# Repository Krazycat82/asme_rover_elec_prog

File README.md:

# ASME-rover-electrical
Circuits and code for ASME Rover team for 2023-24 year

Code for Motor Controllers

Sid was here

Mohamed was here.

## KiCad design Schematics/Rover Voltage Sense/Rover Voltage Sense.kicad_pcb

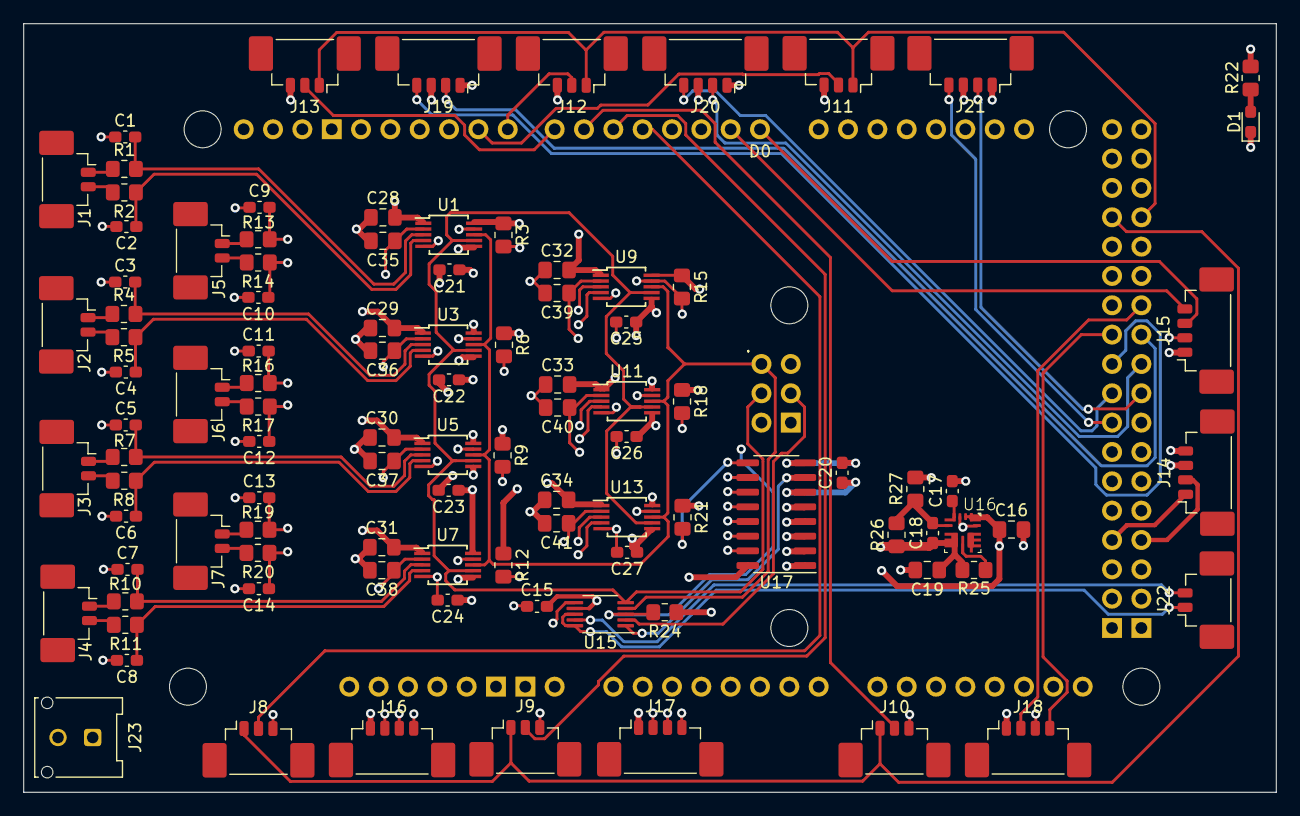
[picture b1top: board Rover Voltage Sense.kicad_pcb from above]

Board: 4 copper layers, 108.5 x 66.5 mm, 102 parts (0 on the bottom side), 77 nets.

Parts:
A1: Arduino_Mega2560_R3_Shield
C1, C2, C3, C4, C5, C6, C7, C8, C9, C10, C11, C12, C13, C14: 2.2n; C_0603_1608Metric_Pad1.08x0.95mm_HandSolder
C15: 100n; C_0603_1608Metric_Pad1.08x0.95mm_HandSolder
C16, C28, C29, C30, C31, C32, C33, C34: 10u; C_0805_2012Metric_Pad1.18x1.45mm_HandSolder
C17: 680p; C_0603_1608Metric_Pad1.08x0.95mm_HandSolder
C18: 10p; C_0603_1608Metric_Pad1.08x0.95mm_HandSolder
C19: 22u; C_0805_2012Metric_Pad1.18x1.45mm_HandSolder
C20, C21, C22, C23, C24, C25, C26, C27: 0.1u; C_0603_1608Metric_Pad1.08x0.95mm_HandSolder
C35, C36, C37, C38, C39, C40, C41: 1u; C_0805_2012Metric_Pad1.18x1.45mm_HandSolder
D1: LED; D_0603_1608Metric_Pad1.05x0.95mm_HandSolder
J1, J2, J3, J4, J5, J6, J7, J22: Conn_01x02; Molex_PicoBlade_53398-0271_1x02-1MP_P1.25mm_Vertical
J8, J9, J10, J11, J12, J13: Conn_01x03; Molex_PicoBlade_53398-0371_1x03-1MP_P1.25mm_Vertical
J14, J15, J16, J17, J18, J19, J20, J21: Conn_01x04; Molex_PicoBlade_53398-0471_1x04-1MP_P1.25mm_Vertical
J23: Conn_01x02; Molex_Micro-Fit_3.0_43045-0212_2x01_P3.00mm_Vertical
R1, R2, R4, R5, R7, R8, R10, R11, R13, R14, R16, R17, R19, R20: 15; R_0805_2012Metric_Pad1.20x1.40mm_HandSolder
R3, R6, R9, R12, R15, R18, R21: 10K; R_0805_2012Metric_Pad1.20x1.40mm_HandSolder
R22: 250; R_0805_2012Metric_Pad1.20x1.40mm_HandSolder
R24: 10k; R_0805_2012Metric_Pad1.20x1.40mm_HandSolder
R25, R27: 100k; R_0805_2012Metric_Pad1.20x1.40mm_HandSolder
R26: 200k; R_0805_2012Metric_Pad1.20x1.40mm_HandSolder
U1, U3, U5, U7, U9, U11, U13: MCP33151; MSOP-10_3x3mm_P0.5mm
U15: INA229; VSSOP-10_3x3mm_P0.5mm
U16: TPSM828512; QFN_FCMOD_RDY00009A
U17: 74HC138; SOIC-16_3.9x9.9mm_P1.27mm

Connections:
+1V8: C18.1, C19.1, C35.1, C36.1, C37.1, C38.1, C39.1, C40.1, C41.1, R25.1, R26.1, U1.2 (AVDD), U3.2 (AVDD), U5.2 (AVDD), U7.2 (AVDD), U9.2 (AVDD), U11.2 (AVDD), U13.2 (AVDD), U16.6 (VOUT)
+5V: A1.5V1 (5V), A1.5V3 (5V), A1.5V4 (5V), C15.2, C16.1, C20.1, C21.1, C22.1, C23.1, C24.1, C25.1, C26.1, C27.1, C28.2, C29.2, C30.2, C31.2, C32.2, C33.2, C34.2, J14.3, J15.1, J16.1, J17.1, J18.1, J19.1, J20.1, J21.1, J23.1, R3.1, R6.1, R9.1, R12.1, R15.1, R18.1, R21.1, R22.1, R24.1, U1.1 (Vref), U1.6 (SDI), U1.10 (DVIO), U3.1 (Vref), U3.6 (SDI), U3.10 (DVIO), U5.1 (Vref), U5.6 (SDI), U5.10 (DVIO), U7.1 (Vref), U7.6 (SDI), U7.10 (DVIO), U9.1 (Vref), U9.6 (SDI), U9.10 (DVIO), U11.1 (Vref), U11.6 (SDI), U11.10 (DVIO), U13.1 (Vref), U13.6 (SDI), U13.10 (DVIO), U15.7 (VS), U16.1 (VIN), U16.2 (EN), U17.6 (E2), U17.16 (VCC)
+BATT: J22.1, U15.8 (VBUS), U15.10 (IN+)
/ADC1/CS: R6.2, U3.9 (CNVST), U17.14 (~Y1)
/ADC2/CS: R9.2, U5.9 (CNVST), U17.13 (~Y2)
/ADC3/CS: R12.2, U7.9 (CNVST), U17.12 (~Y3)
/ADC4/CS: R15.2, U9.9 (CNVST), U17.11 (~Y4)
/ADC5/CS: R18.2, U11.9 (CNVST), U17.10 (~Y5)
/ADC6/CS: R21.2, U13.9 (CNVST), U17.9 (~Y6)
/ADC/CS: R3.2, U1.9 (CNVST), U17.15 (~Y0)
/CLK: A1.SCK (SPI_SCK), U1.7 (SCLK), U3.7 (SCLK), U5.7 (SCLK), U7.7 (SCLK), U9.7 (SCLK), U11.7 (SCLK), U13.7 (SCLK), U15.5 (SCLK)
/Diff_Encoder/ENC-A: A1.D48, J14.1
/Diff_Encoder/ENC-B: A1.D49, J14.2
/MISO: A1.MISO (SPI_MISO), U1.8 (SDO), U3.8 (SDO), U5.8 (SDO), U7.8 (SDO), U9.8 (SDO), U11.8 (SDO), U13.8 (SDO), U15.4 (MISO)
/MOSI: A1.MOSI (SPI_MOSI), U15.2 (MOSI)
/Motor Controller Connectors/DIR_LEFT: A1.D26, J8.1, J9.1, J10.1
/Motor Controller Connectors/DIR_RIGHT: A1.D27, J11.1, J12.1, J13.1
/Motor Controller Connectors/MOTOR_SP1: A1.D4, J8.2
/Motor Controller Connectors/MOTOR_SP2: A1.D5, J9.2
/Motor Controller Connectors/MOTOR_SP3: A1.D6, J10.2
/Motor Controller Connectors/MOTOR_SP4: A1.D7, J13.2
/Motor Controller Connectors/MOTOR_SP5: A1.D8, J12.2
/Motor Controller Connectors/MOTOR_SP6: A1.D9, J11.2
/Motor Encoders/CHA1: A1.D29, J16.2
/Motor Encoders/CHA2: A1.D31, J17.2
/Motor Encoders/CHA3: A1.D33, J18.2
/Motor Encoders/CHA4: A1.D35, J19.2
/Motor Encoders/CHA5: A1.D37, J20.2
/Motor Encoders/CHA6: A1.D39, J21.2
/Motor Encoders/CHB1: A1.D30, J16.4
/Motor Encoders/CHB2: A1.D32, J17.4
/Motor Encoders/CHB3: A1.D34, J18.4
/Motor Encoders/CHB4: A1.D36, J19.4
/Motor Encoders/CHB5: A1.D38, J20.4
/Motor Encoders/CHB6: A1.D40, J21.4
/Mux/A0: A1.D22, U17.1 (A0)
/Mux/A1: A1.D23, U17.2 (A1)
/Mux/A2: A1.D24, U17.3 (A2)
/Mux/EN: A1.D25, U17.5 (~E1)
/Mux/Y7: U15.1 (CS), U17.7 (~Y7)
/Radio/RX: A1.D0 (D0/RX0), J15.3
/Radio/TX: A1.D1 (D1/TX0), J15.4
/Vsense/ALERT: A1.D2 (D2_INT0), R24.2, U15.3 (ALERT)
GND: A1.GND1 (GND), A1.GND2 (GND), A1.GND3 (GND), A1.GND5 (GND), A1.GND6 (GND), C1.1, C2.2, C3.1, C4.2, C5.1, C6.2, C7.1, C8.2, C9.1, C10.2, C11.1, C12.2, C13.1, C14.2, C15.1, C16.2, C17.2, C19.2, C20.2, C21.2, C22.2, C23.2, C24.2, C25.2, C26.2, C27.2, C28.1, C29.1, C30.1, C31.1, C32.1, C33.1, C34.1, C35.2, C36.2, C37.2, C38.2, C39.2, C40.2, C41.2, D1.1 (K), J8.3, J9.3, J10.3, J11.3, J12.3, J13.3, J14.4, J15.2, J16.3, J17.3, J18.3, J19.3, J20.3, J21.3, J23.2, R27.2, U1.5 (GND), U3.5 (GND), U5.5 (GND), U7.5 (GND), U9.5 (GND), U11.5 (GND), U13.5 (GND), U15.6 (GND), U16.3 (MODE_SYNC), U16.9 (GND), U17.4 (~E0), U17.8 (GND)
unnamed: D1.2 (A), R22.2
unnamed: J1.1, R1.1
unnamed: J1.2, R2.1
unnamed: J2.1, R4.1
unnamed: J2.2, R5.1
unnamed: J3.1, R7.1
unnamed: J3.2, R8.1
unnamed: J4.1, R10.1
unnamed: J4.2, R11.1
unnamed: J5.1, R13.1
unnamed: J5.2, R14.1
unnamed: J6.1, R16.1
unnamed: J6.2, R17.1
unnamed: J7.1, R19.1
unnamed: J7.2, R20.1
unnamed: J22.2, U15.9 (IN-)
unnamed: C1.2, R1.2, U1.3 (Ain+)
unnamed: C2.1, R2.2, U1.4 (Ain-)
unnamed: C3.2, R4.2, U3.3 (Ain+)
unnamed: C4.1, R5.2, U3.4 (Ain-)
unnamed: C5.2, R7.2, U5.3 (Ain+)
unnamed: C6.1, R8.2, U5.4 (Ain-)
unnamed: C7.2, R10.2, U7.3 (Ain+)
unnamed: C8.1, R11.2, U7.4 (Ain-)
unnamed: C9.2, R13.2, U9.3 (Ain+)
unnamed: C10.1, R14.2, U9.4 (Ain-)
unnamed: C11.2, R16.2, U11.3 (Ain+)
unnamed: C12.1, R17.2, U11.4 (Ain-)
unnamed: C13.2, R19.2, U13.3 (Ain+)
unnamed: C14.1, R20.2, U13.4 (Ain-)
unnamed: C18.2, R26.2, R27.1, U16.5 (FB)
unnamed: R25.2, U16.7 (PG)
unnamed: C17.1, U16.4 (SS_TR)

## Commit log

2024-09-16 Initial pre fall24 commit
2024-09-19 Code to control motors with keyboard
2024-09-22 New code for transmitter arduino uno
2024-09-26 Arduino Transmitter and Receiver Code
2024-10-17 Added arm code
